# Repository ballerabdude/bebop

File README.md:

# Bebop

Bebop is a wheeled robot built on an NVIDIA Jetson AGX Thor. The current
robot (v3) is a differential-drive base: two ODrive S1 BotWheels with passive
front casters, a Robstride PowerBoard on a 13s2p Li-ion pack, two Orbbec
Gemini 335Lg depth cameras, and a Teensy 4.1 bridge for the mode button and
IMU. Everything runs on the robot, including the voice agent (TensorRT
Edge-LLM). Two Robstride arms come next; the firmware keeps its Robstride
joint path for them. The retired v2 robot was a legged humanoid; its
training and ROS 2 tooling are still in the tree.

This monorepo holds the on-robot services, the operator app and the
workstation tooling around them.

## Architecture

```
 operator app (browser: phone, tablet or desktop)
  │
  ├─ :9091 setup WS ──────────────▶ bebop-agent   Wi-Fi + Hosted Network; mode button via the Teensy
  │
  ├─ :9090 runtime WS + HTTP ─────▶ bebop-linux   100 Hz control loop, safety supervisor, system log
  │                                 ├─ SocketCAN can4 ─▶ 2× ODrive S1 (wheels)
  │                                 ├─ SocketCAN can0 ─▶ Robstride PowerBoard (battery)
  │                                 └─ systemctl ──────▶ bebop-vision, bebop-voice,
  │                                                      bebop-model-download@<id>
  ├─ :9092 video + drive notes ──┐
  ├─ :9095 places ───────────────┴▶ bebop-vision  recorder, WHEP video, place memory; owns the cameras
  ├─ :9093 voice WS ──────────────▶ bebop-voice   agent gateway: ASR → brain → TTS, or Qwen3-Omni
  └─ :9094 models HTTP ───────────▶ bebop-models  GPU budget + Edge-LLM model lifecycle
```

Every service is a systemd unit on the Thor (JetPack 7.2 / L4T R39.2.1,
CUDA 13.2, Python 3.12). The recorder and the voice agent are clients of the
runtime API too. Ports, boot order and who runs as root are in
[`docs/architecture.md`](docs/architecture.md).

## Repository layout

| Path | What it is |
|---|---|
| `firmware/bebop-linux/` | The robot runtime (Rust): SocketCAN supervisor for the ODrive wheels, the PowerBoard and the Robstride joint path; the runtime WebSocket/HTTP API on `:9090`; the always-on system log; the `sysid` single-joint actuator bench. |
| `firmware/bebop-locomotion/` | Teensy 4.1 firmware (PlatformIO). `teensy_bridge` is the production env: BNO085 IMU frames and mode-button events over USB serial. `sim` and `ros` are the legacy micro-ROS controller of an earlier wheel-legged robot (hip and knee Robstrides plus wheels); `imu_test` and `imu_spi_test` are standalone BNO085 checks (I2C, SPI). |
| `jetson-agent/` | Rust workspace: `bebop-agent` (Wi-Fi and Hosted Network provisioning, the mode button, the setup server on `:9091`), `bebop-proto` (the setup and runtime protobuf schemas), `deploy/` (agent unit and install scripts). |
| `bebop-vision/` | Python, one venv on the robot: the recorder (navd MCAP sessions), operator video (WHEP on `:9092`, `/snapshot`, drive notes), place memory (`:9095`), the voice gateway (`:9093`), the model supervisor (`:9094`) and weight downloads; plus the labeling and dataset tools (SAM 3.1 × depth labels, MCAP extraction, capture pull, session ledger). |
| `bebop-app/` | The operator app (React + TypeScript + Vite): setup wizard, driving, agent console, place memory, diagnostics, settings. `src-tauri/` is an unused Tauri 2 shell. |
| `scripts/` | `install-jetson.sh` (installs and upgrades the robot stack), `setup-rerun.sh` (on-robot MCAP → Rerun conversion), `build-gs-usb.sh`, the GPU-clocks unit, Orbbec udev rules. |
| `rerun_dashboards/` | MCAP → Rerun `.rrd` conversion and the navd and system dashboards (`open.py`). |
| `foxglove/` | Foxglove layouts: navd sessions, plus layouts for the retired v2 policy captures. |
| `sim/` | Isaac Sim / Isaac Lab training for the retired v2 humanoid (`bebop_training`), the Robstride sysid and actuator-net fitting tools, kept for the arms (`bebop_training/tools/`), and the on-device Thor training env (`setup/thor/`). |
| `ros2/` | The v2 humanoid's ROS 2 Jazzy dev workspace (URDF, `bebop_pilot`, micro-ROS agent container). Legacy. |
| `bebop-mb/` | KiCad motherboard joining the Orin Nano's 40-pin header, a Teensy 4.1, a BNO085 and a CAN transceiver. Orin Nano era. |
| `jetson-flash/` | Host-side L4T download and flash for the Orin Nano devkit. Stale for the Thor: its board config and flash commands are Orin-only. |
| `fusion-scripts/` | Fusion 360 helper scripts (hide sketches, merge bodies, rename bodies, set mass). |
| `docs/` | Cross-cutting docs; index in [`docs/README.md`](docs/README.md). |
| `docker-compose.yml` | Workstation containers `ros2_docker`, `isaac_sim`, `isaac_lab` (profiles `sim`, `lab`). |
| `Caddyfile.dev` | Dev TLS proxy for the app ([`docs/dev-https.md`](docs/dev-https.md)). |
| `justfile` | Recipes; `just` lists them. |
| `.github/workflows/ci.yml` | CI: fmt, clippy and tests for both Rust workspaces, arm64 release builds, firmware Releases on `firmware/v*` tags. |
| `AGENTS.md` | Working notes: robot access, deploy process, gotchas. |

## Getting started

[`docs/onboarding.md`](docs/onboarding.md) covers workstation setup, tests
and installing on the robot. The common recipes:

```sh
just                           # list recipes
just check                     # jetson-agent: cargo check
just test                      # jetson-agent: cargo test
just lint                      # jetson-agent: clippy, warnings are errors
just app-web                   # operator app on the Vite dev server (:1420)
just build-jetson              # bebop-agent release build (arm64 Linux only)
just deploy bebop@bebop.local  # install that bebop-agent build on the robot
just pull-data                 # mirror captures from the robot, extract, write the ledger
```

The firmware has no recipe: `cd firmware/bebop-linux && cargo test` (Linux,
`protoc` installed). On the robot, `sudo ./scripts/install-jetson.sh`
installs `bebop-agent`, `bebop-linux` and the service units.

`just fw-build` and `just fw-flash` use PlatformIO's default env (`sim`), not
the robot's `teensy_bridge`. Flash the Teensy with
`cd firmware/bebop-locomotion && pio run -e teensy_bridge --target upload`.

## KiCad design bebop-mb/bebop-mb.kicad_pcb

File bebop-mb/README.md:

# Bebop Motherboard (`bebop-mb`)

KiCad 10 project for the **Bebop Connector / motherboard** board. It is the interconnect
between an **NVIDIA Jetson Orin Nano** carrier board, a **Teensy 4.1** microcontroller, a
**Bosch BNO085 9‑DoF IMU** (Adafruit breakout), and a **CAN bus** front end. The board mostly
provides headers/breakouts and routes shared buses between these modules.

> Silkscreen title block: *"Bebop Connector"*.

## Schematic sheets

| Sheet file | Contents |
|---|---|
| `bebop-mb.kicad_sch` | Root sheet: BNO085 IMU header (`J8`) + IMU breakouts (`J11`/`J12`), CAN connectors (`J1`–`J4`), mounting holes, power |
| `teensy-mcu.kicad_sch` | Teensy 4.1 (`U1`) and its two breakout headers (`J6`/`J7`) |
| `jetson-interface.kicad_sch` | Jetson 40‑pin IDC header (`J5`) and its two breakout headers (`J9`/`J10`) |
| `can-transceiver.kicad_sch` | SN65HVD230 CAN transceiver (`U2`) + decoupling (`C14`) |

## Component / connector reference

| Ref | Part / type | Footprint | Purpose |
|---|---|---|---|
| `U1` | Teensy 4.1 (48‑pin THT, 2×24) | `bebop-mb:Teensy41_Simple` | Main MCU |
| `J6` | 1×24 socket | `PinSocket_1x24` | Teensy left row breakout (Teensy pins 1–24) |
| `J7` | 1×24 socket | `PinSocket_1x24` | Teensy right row breakout (Teensy pins 25–48) |
| `J5` | 2×20 IDC box header | `Connector_IDC:IDC-Header_2x20_P2.54mm_Vertical` | Ribbon to Jetson 40‑pin header |
| `J9` | 1×20 socket | `PinSocket_1x20` | Jetson **odd** pins (1,3,…,39) breakout |
| `J10` | 1×20 socket | `PinSocket_1x20` | Jetson **even** pins (2,4,…,40) breakout |
| `J8` | BNO085 breakout header (2×6) | `bebop-mb:BNO08x_Breakout` | Adafruit BNO085 IMU |
| `J11` | 1×6 socket | `PinSocket_1x6` | BNO085 primary‑pin breakout (VIN/3Vo/GND/SCL/SDA/INT) |
| `J12` | 1×6 socket | `PinSocket_1x6` | BNO085 secondary‑pin breakout (BT/P0/P1/RST/DI/CS) |
| `U2` | SN65HVD230 (SOIC‑8) | — | 3.3 V CAN transceiver |
| `C14` | 100 nF | `C_0603` | `U2` decoupling |
| `J1` | 3‑pin screw terminal | `TerminalBlock_Xinya XY308 3P` | CAN bus (CANH/CANL/GND) |
| `J2`,`J3`,`J4` | JST‑GH 2‑pin | `JST_GH_SM02B-GHS-TB` | CAN bus daisy‑chain (CANH/CANL) |
| `H1`–`H4` | M3 mounting holes | `MountingHole_3.2mm_M3` | Mechanical |

## Power rails

| Net | Notes |
|---|---|
| `+3.3V` | Main logic rail. Feeds BNO085 `VIN`, CAN transceiver `U2`, and the BNO `P0`/`P1` mode straps |
| `GND` | Common ground |
| `Vin` | Teensy `Vin` (broken out on `J7` pin 1) |

The Jetson 40‑pin header also exposes its own `3.3V` (pins 1, 17) and `5.0V` (pins 2, 4) on
`J9`/`J10`; these are **not** tied to the board `+3.3V` rail unless you bridge them.

---

## Teensy 4.1 (`U1`) → breakouts `J6` / `J7`

`J6`/`J7` are 1×24 socket breakouts; **`J6` pad N = Teensy pin N**, **`J7` pad N = Teensy pin N+24**.
Silkscreen on `J6`/`J7` shows the Teensy pin name.

### Active Teensy connections

| Function | Teensy pin (GPIO) | Breakout | Net |
|---|---|---|---|
| IMU SPI clock | 13 (SCK/LED) | `J7` pad 14 | `IMU_SCK` |
| IMU SPI MISO | 12 | `J6` pad 14 | `IMU_MISO` |
| IMU SPI MOSI | 11 | `J6` pad 13 | `IMU_MOSI` |
| IMU SPI CS | 10 | `J6` pad 12 | `IMU_CS` |
| IMU interrupt | 37 | `J7` pad 20 | `IMU_INT` |
| IMU reset | 36 | `J7` pad 21 | `IMU_RST` |
| CAN1 TX (CTX1) | 22 | `J7` pad 5 | `CAN1_TX` |
| CAN1 RX (CRX1) | 23 | `J7` pad 4 | `CAN1_RX` |
| I²C SCL (spare) | 19 (A5/SCL) | `J7` pad 8 | `IMU_SCL` |
| I²C SDA (spare) | 18 (A4/SDA) | `J7` pad 9 | `IMU_SDA` |

> `IMU_SCL`/`IMU_SDA` are the legacy I²C pins. The IMU was migrated to **SPI**, so these are
> now just an unused I²C bus broken out on `J7`.

---

## BNO085 IMU (`J8`) — wired for SPI

The BNO085 is configured for **SPI** (not I²C). Protocol is selected by tying `P0`/`P1` high.

| `J8` pin | BNO pad | SPI role | Net |
|---|---|---|---|
| 1 | VIN | power | `+3.3V` |
| 3 | GND | ground | `GND` |
| 4 | SCL | SCK (clock) | `IMU_SCK` |
| 5 | SDA | MISO (sensor → host) | `IMU_MISO` |
| 11 | DI | MOSI (host → sensor) | `IMU_MOSI` |
| 12 | CS | chip select | `IMU_CS` |
| 6 | INT | data‑ready | `IMU_INT` |
| 10 | RST | reset | `IMU_RST` |
| 8 | P0 (PS0) | mode select → **high** | `+3.3V` |
| 9 | P1 (PS1) | mode select → **high** | `+3.3V` |
| 2 | 3Vo | BNO 3.3 V out (breakout only) | — |
| 7 | BT | boot (breakout only) | `J12` pin 1 |

`J11` breaks out the primary row (VIN/3Vo/GND/SCL/SDA/INT) and `J12` the secondary row
(BT/P0/P1/RST/DI/CS); both simply follow whatever `J8` carries.

---

## Shared IMU SPI bus (Teensy **and** Jetson)

The BNO085 SPI bus is wired **in parallel** to both the Teensy and the Jetson so either can act
as master. They must **not** be active at the same time.

```
            IMU_SCK / IMU_MISO / IMU_MOSI / IMU_CS / IMU_INT / IMU_RST
                                  |
        +---------------+---------+---------+----------------+
        |               |                   |                |
   BNO085 (J8)     Teensy U1           Jetson J5         Breakouts
                (13/12/11/10,        (SPI0 + GPIO,      (J6/J7, J9/J10,
                 37/36)               see below)         J11/J12)
```

| Signal | BNO085 | Teensy 4.1 | Jetson 40‑pin |
|---|---|---|---|
| SCK | SCL | GPIO13 | pin 23 (SPI0_SCK) |
| MISO | SDA | GPIO12 | pin 21 (SPI0_MISO) |
| MOSI | DI | GPIO11 | pin 19 (SPI0_MOSI) |
| CS | CS | GPIO10 | pin 24 (SPI0_CS0\*) |
| INT | INT | GPIO37 | pin 7 (GPIO09) |
| RST | RST | GPIO36 | pin 15 (GPIO12) |

> ⚠️ **Bus contention:** there is no hardware isolation (no mux/buffer) between the two masters.
> Firmware must keep the **inactive** master's SCK/MOSI/CS (and INT/RST) pins as **high‑impedance
> inputs** so the two masters never drive the bus simultaneously.

---

## Jetson 40‑pin header (`J5`) → breakouts `J9` / `J10`

`J5` is a 2×20 IDC box header (ribbon to the Jetson carrier 40‑pin expansion header).
`J9` breaks out the **odd** column, `J10` the **even** column. Silkscreen on `J9`/`J10` is
`<Jetson pin #> <signal>`.

| Pin | Signal | | Pin | Signal |
|---:|---|---|---:|---|
| 1 | 3.3V | | 2 | 5.0V |
| 3 | I2C1_SDA | | 4 | 5.0V |
| 5 | I2C1_SCL | | 6 | GND |
| 7 | GPIO09 → **IMU_INT** | | 8 | UART1_TXD |
| 9 | GND | | 10 | UART1_RXD |
| 11 | UART1_RTS\* | | 12 | I2S0_SCLK |
| 13 | SPI1_SCK | | 14 | GND |
| 15 | GPIO12 → **IMU_RST** | | 16 | SPI1_CS1\* |
| 17 | 3.3V | | 18 | SPI1_CS0\* |
| 19 | SPI0_MOSI → **IMU_MOSI** | | 20 | GND |
| 21 | SPI0_MISO → **IMU_MISO** | | 22 | SPI1_MISO |
| 23 | SPI0_SCK → **IMU_SCK** | | 24 | SPI0_CS0\* → **IMU_CS** |
| 25 | GND | | 26 | SPI0_CS1\* |
| 27 | I2C0_SDA | | 28 | I2C0_SCL |
| 29 | GPIO01 | | 30 | GND |
| 31 | GPIO11 | | 32 | GPIO07 |
| 33 | GPIO13 | | 34 | GND |
| 35 | I2S0_FS | | 36 | UART1_CTS\* |
| 37 | SPI1_MOSI | | 38 | I2S0_DIN |
| 39 | GND | | 40 | I2S0_DOUT |

Pins in **bold** are routed to the shared IMU bus; all other pins are simply broken out on
`J9`/`J10` for access.

---

## CAN bus (`U2` + `J1`–`J4`)

`U2` (SN65HVD230, 3.3 V) bridges the Teensy CAN1 controller to the physical bus.

| `U2` side | Connects to |
|---|---|
| `D` (driver in) | `CAN1_TX` ← Teensy GPIO22 (CTX1) |
| `R` (receiver out) | `CAN1_RX` → Teensy GPIO23 (CRX1) |
| `CANH` / `CANL` | CAN connectors `J1`–`J4` |
| `VCC` / `GND` | `+3.3V` / `GND` |

- `J1` — 3‑pin screw terminal: **CANH / CANL / GND**.
- `J2`, `J3`, `J4` — JST‑GH 2‑pin: **CANH / CANL** (for daisy‑chaining nodes).

Add a 120 Ω termination resistor at the bus ends as needed (not currently populated on‑board).

---

## Notes

- This board is KiCad 10 (name‑based nets; no numbered net table).
- After editing any schematic sheet, run **Tools → Update PCB from Schematic** and re‑run **DRC**.
- The IMU SPI bus sharing relies on firmware discipline (see the contention warning above); if you
  want hardware‑guaranteed isolation, add series resistors or a GPIO/jumper‑selected SPI bus switch.

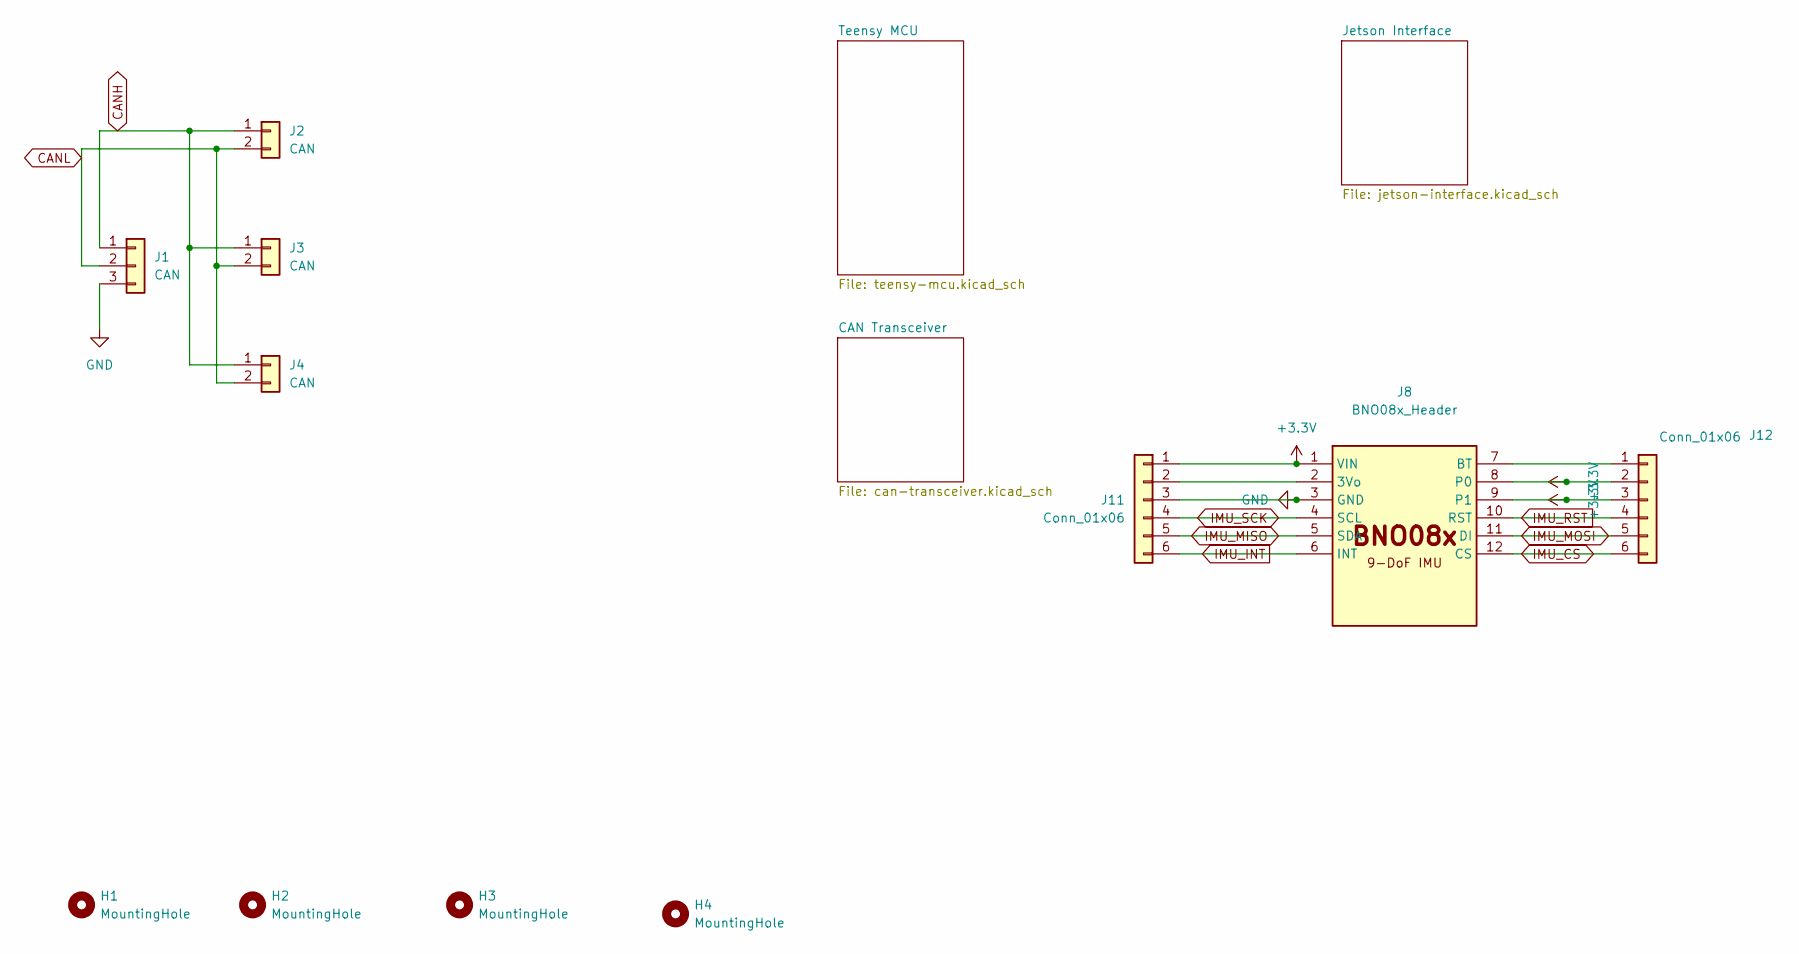
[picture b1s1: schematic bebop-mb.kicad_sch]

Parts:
H1, H2, H3, H4: MountingHole; MountingHole_3.2mm_M3_ISO14580
J1: CAN; TerminalBlock_Xinya_XY308-2.54-3P_1x03_P2.54mm_Horizontal; Manufacturer Part Number XY308-3P
J2, J3, J4: CAN; JST_GH_SM02B-GHS-TB_1x02-1MP_P1.25mm_Horizontal; Manufacturer Part Number SM02B-GHS-TB(LF)(SN)
J8: BNO08x_Header; BNO08x_Breakout; Manufacturer Part Number PPTC061LFBN-RC
J11, J12: Conn_01x06; PinSocket_1x06_P2.54mm_Vertical; Manufacturer Part Number PPTC061LFBN-RC

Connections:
+3.3V: J8.1 (VIN), J8.8 (P0), J8.9 (P1), J11.1, J12.2, J12.3; also elsewhere on the board
CANH: J1.1, J2.1, J3.1, J4.1; also elsewhere on the board
CANL: J1.2, J2.2, J3.2, J4.2; also elsewhere on the board
GND: J1.3, J8.3 (GND), J11.3; also elsewhere on the board
IMU_CS: J8.12 (CS), J12.6; also elsewhere on the board
IMU_INT: J8.6 (INT), J11.6; also elsewhere on the board
IMU_MISO: J8.5 (SDA), J11.5; also elsewhere on the board
IMU_MOSI: J8.11 (DI), J12.5; also elsewhere on the board
IMU_RST: J8.10 (RST), J12.4; also elsewhere on the board
IMU_SCK: J8.4 (SCL), J11.4; also elsewhere on the board
unnamed: J8.2 (3Vo), J11.2
unnamed: J8.7 (BT), J12.1

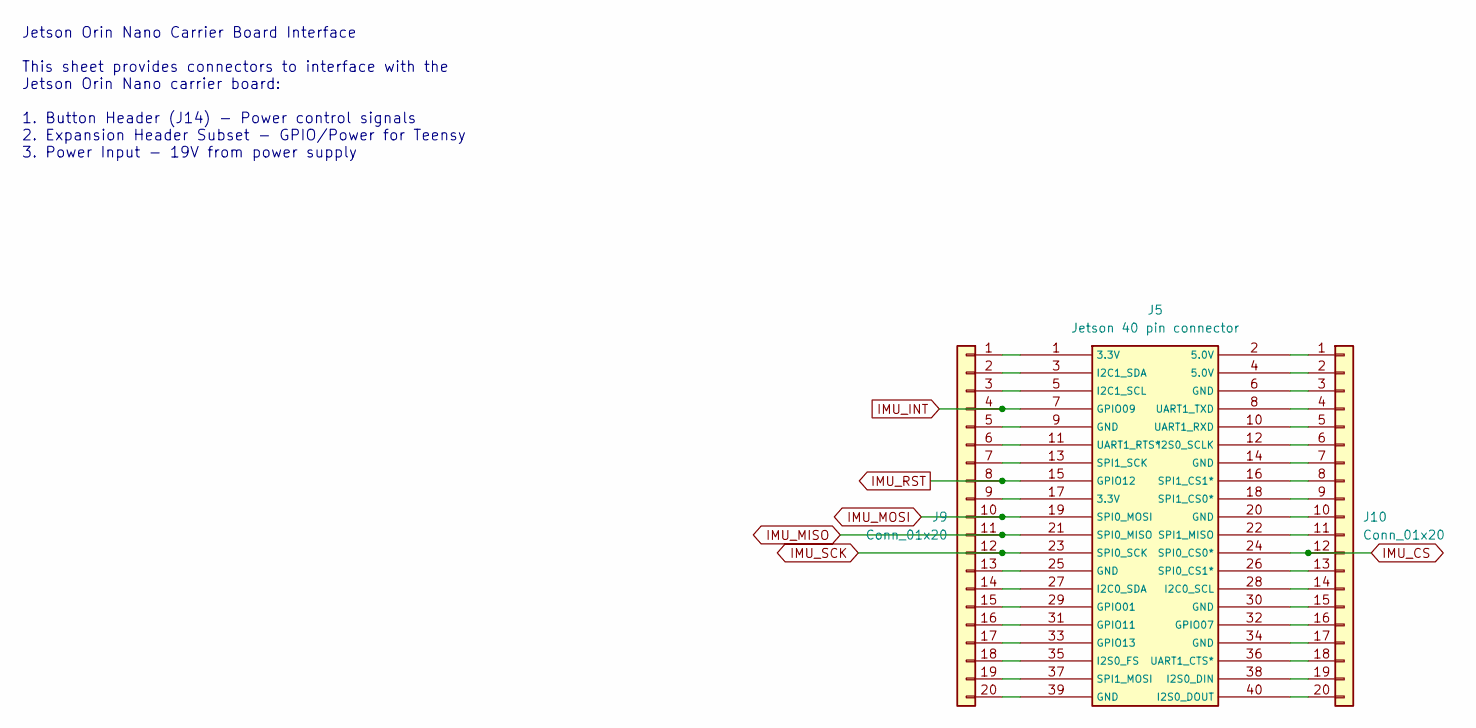
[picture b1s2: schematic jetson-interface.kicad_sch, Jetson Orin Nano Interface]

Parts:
J5: Jetson 40 pin connector; IDC-Header_2x20_P2.54mm_Vertical; Manufacturer Part Number PPTC202LFBN-RC
J9, J10: Conn_01x20; PinSocket_1x20_P2.54mm_Vertical; Manufacturer Part Number PPTC201LFBN-RC

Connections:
IMU_CS: J5.24 (SPI0_CS0*), J10.12; also elsewhere on the board
IMU_INT: J5.7 (GPIO09), J9.4; also elsewhere on the board
IMU_MISO: J5.21 (SPI0_MISO), J9.11; also elsewhere on the board
IMU_MOSI: J5.19 (SPI0_MOSI), J9.10; also elsewhere on the board
IMU_RST: J5.15 (GPIO12), J9.8; also elsewhere on the board
IMU_SCK: J5.23 (SPI0_SCK), J9.12; also elsewhere on the board
unnamed: J5.29 (GPIO01), J9.15
unnamed: J5.31 (GPIO11), J9.16
unnamed: J5.33 (GPIO13), J9.17
unnamed: J5.27 (I2C0_SDA), J9.14
unnamed: J5.5 (I2C1_SCL), J9.3
unnamed: J5.3 (I2C1_SDA), J9.2
unnamed: J5.35 (I2S0_FS), J9.18
unnamed: J5.37 (SPI1_MOSI), J9.19
unnamed: J5.13 (SPI1_SCK), J9.7
unnamed: J5.11 (UART1_RTS*), J9.6
unnamed: J5.1 (3.3V), J9.1
unnamed: J5.9 (GND), J9.5
unnamed: J5.17 (3.3V), J9.9
unnamed: J5.25 (GND), J9.13
unnamed: J5.39 (GND), J9.20
unnamed: J5.2 (5.0V), J10.1
unnamed: J5.4 (5.0V), J10.2
unnamed: J5.6 (GND), J10.3
unnamed: J5.8 (UART1_TXD), J10.4
unnamed: J5.10 (UART1_RXD), J10.5
unnamed: J5.12 (I2S0_SCLK), J10.6
unnamed: J5.14 (GND), J10.7
unnamed: J5.16 (SPI1_CS1*), J10.8
unnamed: J5.18 (SPI1_CS0*), J10.9
unnamed: J5.20 (GND), J10.10
unnamed: J5.22 (SPI1_MISO), J10.11
unnamed: J5.26 (SPI0_CS1*), J10.13
unnamed: J5.28 (I2C0_SCL), J10.14
unnamed: J5.30 (GND), J10.15
unnamed: J5.32 (GPIO07), J10.16
unnamed: J5.34 (GND), J10.17
unnamed: J5.36 (UART1_CTS*), J10.18
unnamed: J5.38 (I2S0_DIN), J10.19
unnamed: J5.40 (I2S0_DOUT), J10.20

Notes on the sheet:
Jetson Orin Nano Carrier Board Interface This sheet provides connectors to interface with the Jetson Orin Nano carrier board: 1. Button Header (J14) - Power control signals 2. Expansion Header Subset - GPIO/Power for Teensy 3. Power Input - 19V from power supply

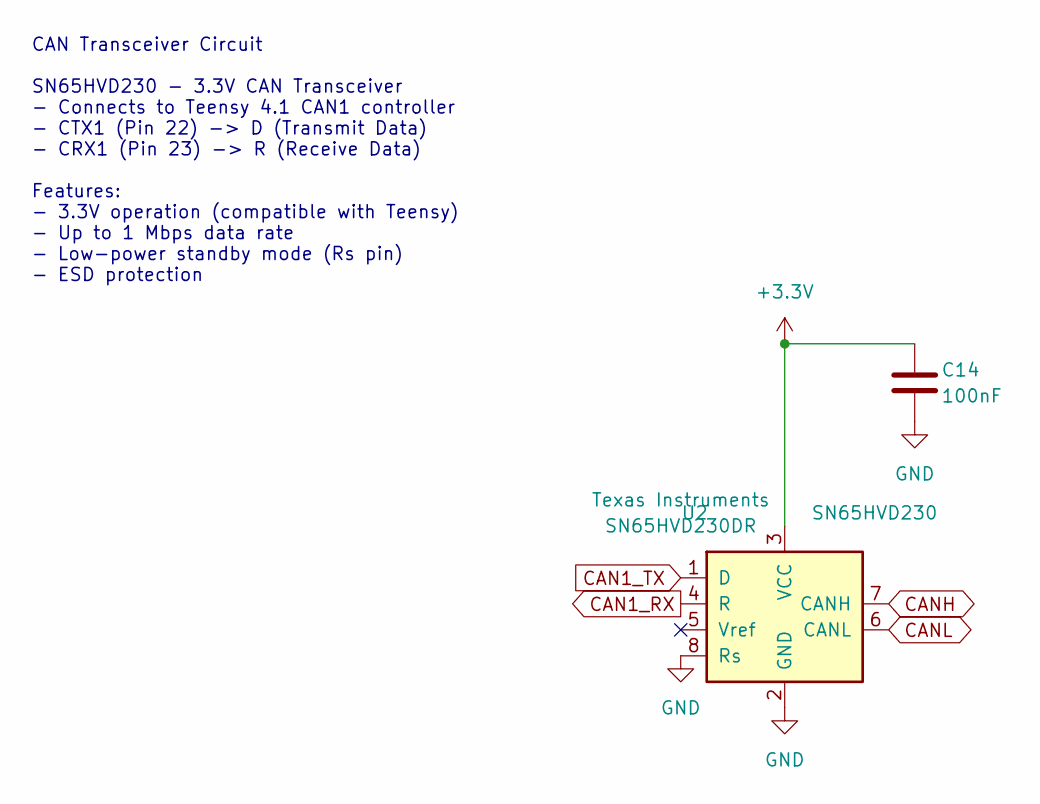
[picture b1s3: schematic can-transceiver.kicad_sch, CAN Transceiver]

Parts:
C14: 100nF; C_0603_1608Metric; Manufacturer Part Number GRM188R71H104KA93D
U2: SN65HVD230; SOIC-8_3.9x4.9mm_P1.27mm; Manufacturer Part Number SN65HVD230DR

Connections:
+3.3V: C14.1, U2.3 (VCC); also elsewhere on the board
CAN1_RX: U2.4 (R); also elsewhere on the board
CAN1_TX: U2.1 (D); also elsewhere on the board
CANH: U2.7 (CANH); also elsewhere on the board
CANL: U2.6 (CANL); also elsewhere on the board
GND: C14.2, U2.2 (GND), U2.8 (Rs); also elsewhere on the board

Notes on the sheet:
CAN Transceiver Circuit SN65HVD230 - 3.3V CAN Transceiver - Connects to Teensy 4.1 CAN1 controller - CTX1 (Pin 22) -> D (Transmit Data) - CRX1 (Pin 23) -> R (Receive Data) Features: - 3.3V operation (compatible with Teensy) - Up to 1 Mbps data rate - Low-power standby mode (Rs pin) - ESD protection

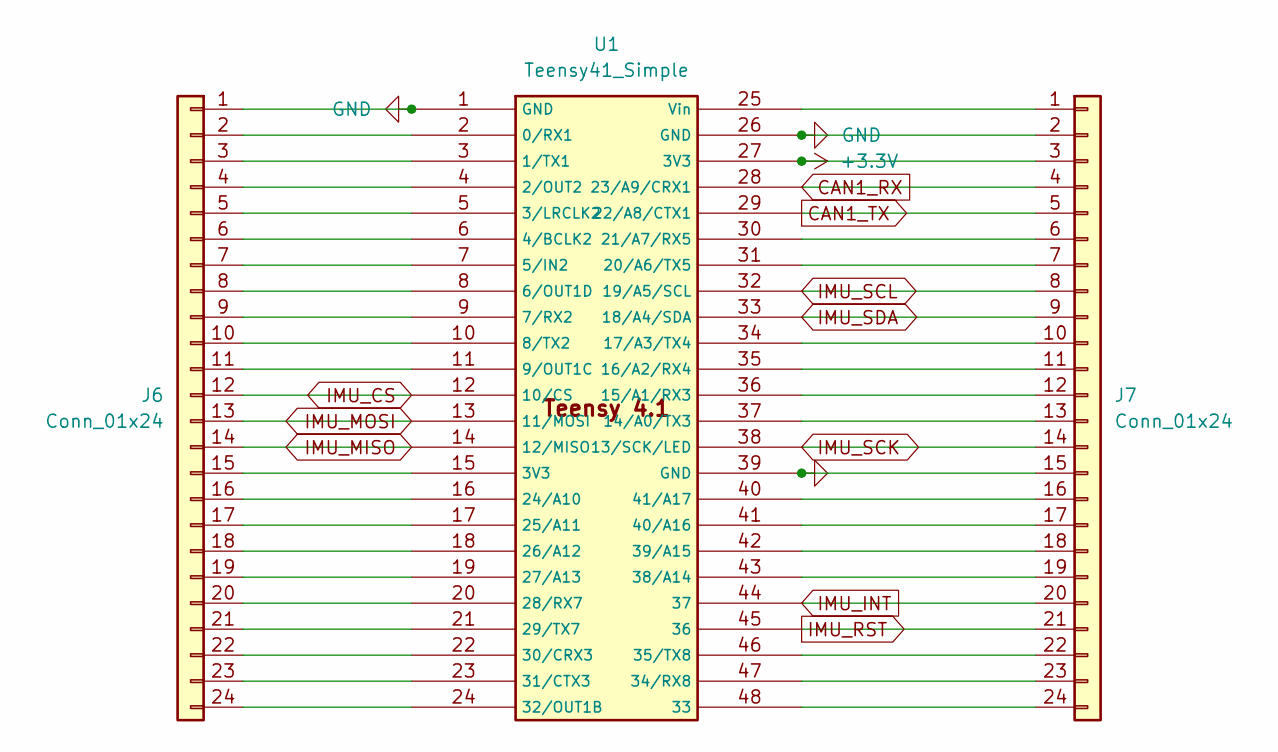
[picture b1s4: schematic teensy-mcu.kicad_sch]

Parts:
J6, J7: Conn_01x24; PinSocket_1x24_P2.54mm_Vertical; Manufacturer Part Number PPTC241LFBN-RC
U1: Teensy41_Simple; Manufacturer Part Number PPTC241LFBN-RC

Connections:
+3.3V: J7.3, U1.27 (3V3); also elsewhere on the board
CAN1_RX: J7.4, U1.28 (23/A9/CRX1); also elsewhere on the board
CAN1_TX: J7.5, U1.29 (22/A8/CTX1); also elsewhere on the board
GND: J6.1, J7.2, J7.15, U1.1 (GND), U1.26 (GND), U1.39 (GND); also elsewhere on the board
IMU_CS: J6.12, U1.12 (10/CS); also elsewhere on the board
IMU_INT: J7.20, U1.44 (37); also elsewhere on the board
IMU_MISO: J6.14, U1.14 (12/MISO); also elsewhere on the board
IMU_MOSI: J6.13, U1.13 (11/MOSI); also elsewhere on the board
IMU_RST: J7.21, U1.45 (36); also elsewhere on the board
IMU_SCK: J7.14, U1.38 (13/SCK/LED); also elsewhere on the board
IMU_SCL: J7.8, U1.32 (19/A5/SCL)
IMU_SDA: J7.9, U1.33 (18/A4/SDA)
unnamed: J6.2, U1.2 (0/RX1)
unnamed: J6.3, U1.3 (1/TX1)
unnamed: J6.4, U1.4 (2/OUT2)
unnamed: J6.5, U1.5 (3/LRCLK2)
unnamed: J6.6, U1.6 (4/BCLK2)
unnamed: J6.7, U1.7 (5/IN2)
unnamed: J6.8, U1.8 (6/OUT1D)
unnamed: J6.9, U1.9 (7/RX2)
unnamed: J6.10, U1.10 (8/TX2)
unnamed: J6.11, U1.11 (9/OUT1C)
unnamed: J6.15, U1.15 (3V3)
unnamed: J6.16, U1.16 (24/A10)
unnamed: J6.17, U1.17 (25/A11)
unnamed: J6.18, U1.18 (26/A12)
unnamed: J6.19, U1.19 (27/A13)
unnamed: J6.20, U1.20 (28/RX7)
unnamed: J6.21, U1.21 (29/TX7)
unnamed: J6.22, U1.22 (30/CRX3)
unnamed: J6.23, U1.23 (31/CTX3)
unnamed: J6.24, U1.24 (32/OUT1B)
unnamed: J7.1, U1.25 (Vin)
unnamed: J7.6, U1.30 (21/A7/RX5)
unnamed: J7.7, U1.31 (20/A6/TX5)
unnamed: J7.10, U1.34 (17/A3/TX4)
unnamed: J7.11, U1.35 (16/A2/RX4)
unnamed: J7.12, U1.36 (15/A1/RX3)
unnamed: J7.13, U1.37 (14/A0/TX3)
unnamed: J7.16, U1.40 (41/A17)
unnamed: J7.17, U1.41 (40/A16)
unnamed: J7.18, U1.42 (39/A15)
unnamed: J7.19, U1.43 (38/A14)
unnamed: J7.22, U1.46 (35/TX8)
unnamed: J7.23, U1.47 (34/RX8)
unnamed: J7.24, U1.48 (33)

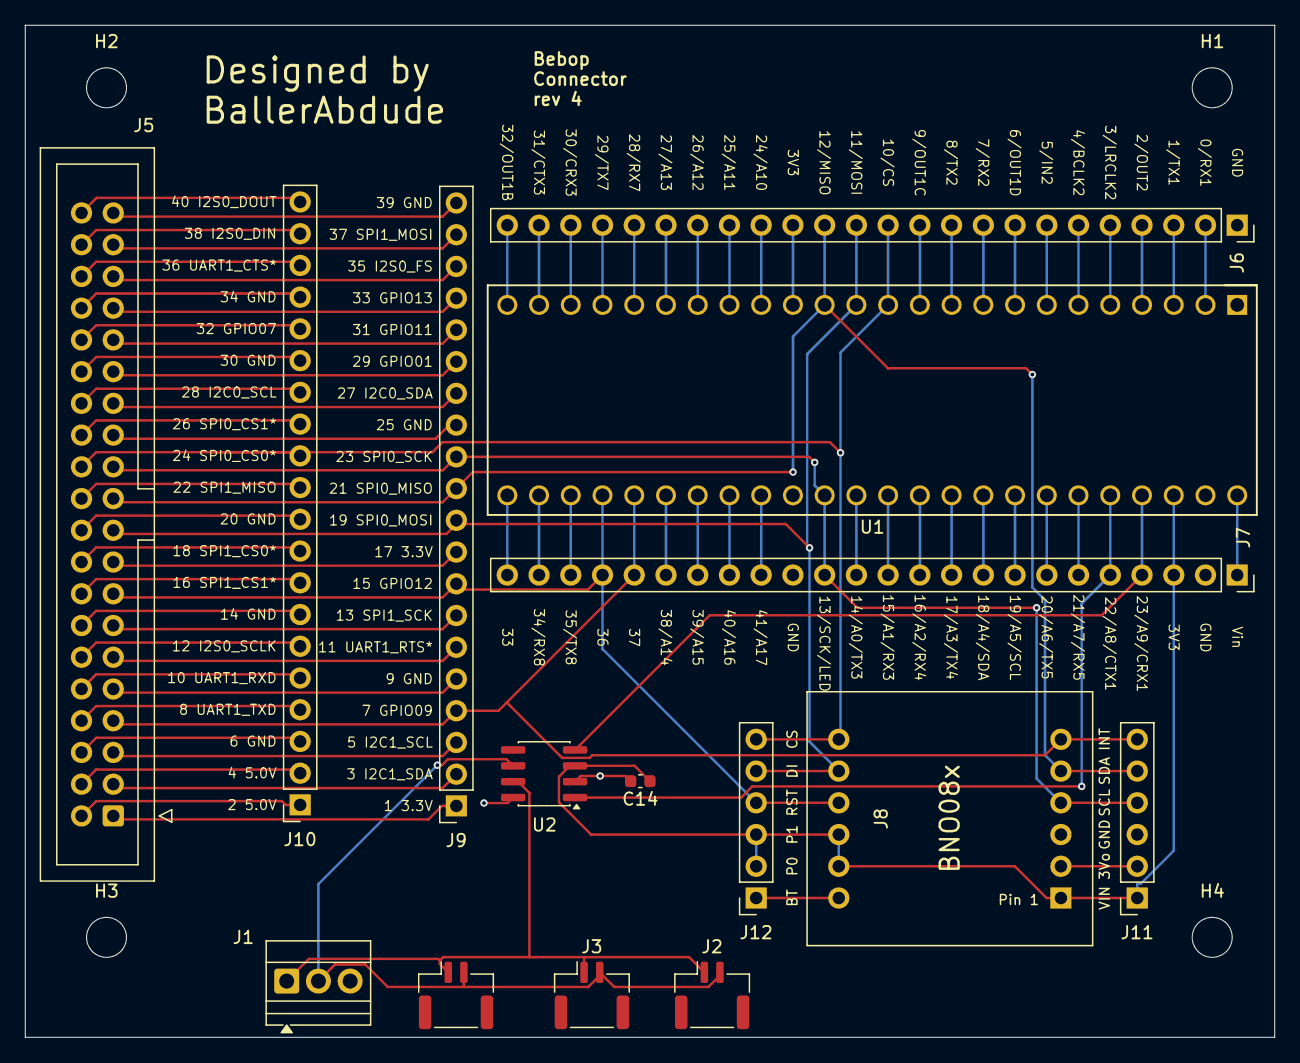
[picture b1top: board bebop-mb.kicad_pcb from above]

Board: 2 copper layers, 100.0 x 81.0 mm, 19 parts (0 on the bottom side), 84 nets.

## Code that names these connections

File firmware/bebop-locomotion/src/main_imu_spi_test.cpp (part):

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// CONFIGURATION
// ============================================================================

#define IMU_CS_PIN    10       // SPI chip select
#define IMU_INT_PIN   37       // REQUIRED for SPI
#define IMU_RST_PIN   36       // reset (constructor)
#define REPORT_INTERVAL_US 5000   // 5ms -> 200Hz requested report rate

// Use the primary USB serial for all output.
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// ============================================================================

// Reset pin is supplied to the constructor; CS/INT go to begin_SPI().
Adafruit_BNO08x bno(IMU_RST_PIN);
sh2_SensorValue_t sensorValue;

float quat_w = 1, quat_x = 0, quat_y = 0, quat_z = 0;
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// low when it has data to send / is ready. If INT never moves, the sensor is
// likely unpowered, not in SPI mode (PS1/PS0), or INT is miswired.
void probeIntPin() {
    pinMode(IMU_INT_PIN, INPUT_PULLUP);
    OUT.printf("[SPI] Sampling INT pin (%d) for 500ms...\n", IMU_INT_PIN);
    int lows = 0, highs = 0;
    uint32_t t0 = millis();
    while (millis() - t0 < 500) {
        if (digitalRead(IMU_INT_PIN) == LOW) lows++; else highs++;
        delayMicroseconds(200);
    }
    OUT.printf("[SPI]   INT samples: LOW=%d HIGH=%d %s\n", lows, highs,
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    probeIntPin();

    OUT.printf("[IMU] Initializing BNO085 over SPI (CS=%d, INT=%d, RST=%d)...\n",
               IMU_CS_PIN, IMU_INT_PIN, IMU_RST_PIN);

    if (!bno.begin_SPI(IMU_CS_PIN, IMU_INT_PIN, &SPI)) {
        OUT.println(F("[IMU] begin_SPI() FAILED."));
        OUT.println(F("[IMU]   -> Confirm PS1=1, PS0=1 (SPI mode)."));
        OUT.println(F("[IMU]   -> Confirm SCK=13, MOSI=11, MISO=12, CS, INT, RST."));
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    // read entirely when INT is high.
    int drained = 0;
    while (drained < MAX_EVENTS_PER_LOOP &&
           digitalRead(IMU_INT_PIN) == LOW &&
           bno.getSensorEvent(&sensorValue)) {
        drained++;
        event_count++;
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
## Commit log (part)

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2026-04-30 style(jetson-agent): apply rustfmt to ble::server
    Reflows three method chains in `bebop-agent/src/ble/server.rs` that the
    current pinned rustfmt (1.90.0) collapses onto a single line. No
    semantic changes; `cargo fmt --all -- --check` is now clean across the
    workspace.
2026-05-01 ci(jetson-agent): install modern protoc in cross image
    The default `cross` aarch64-unknown-linux-gnu image is based on Ubuntu
    16.04, whose `protobuf-compiler` package is protoc 2.6.1 and rejects
    `syntax = "proto3"`. Drop the apt package and fetch a current protoc
    release binary into /usr/local during pre-build so bebop-proto's
    build.rs can compile bebop.proto under cross.
    Made-with: Cursor
2026-05-01 chore(jetson-agent): mark deploy scripts executable
    So `sudo ./jetson-agent/deploy/scripts/install.sh ...` works directly
    on a fresh clone without needing `chmod +x` first (or invoking via
    `bash`). Matches how every other shell entrypoint in the repo is
    expected to be run.
    Made-with: Cursor
2026-05-01 fix(bebop-app): improve Wi-Fi network selection UX
    The picker was confusing in real environments:
    - Multi-AP and dual-band networks showed up multiple times because nmcli
    returns one row per BSSID. Dedupe by (ssid, security), keeping the
    strongest signal, so each SSID renders once.
    - Tapping the already-connected network walked the user through the
    password prompt again, even though the agent already has working
2026-05-01 fix(bebop-app): make BLE transport reliable and friendly
    A handful of bugs surfaced while exercising the setup flow on real
    hardware. They all sit in the BLE transport layer and the screens that
    drive it; bundling here so each individual fix has the others as
    context.
    Tauri / btleplug central (src-tauri/src/ble/central.rs):
    - Open the notification stream synchronously inside connect() before
2026-05-05 ci: build bebop-linux alongside bebop-agent
    Mirrors the agent's two-job pattern (host checks + native arm64
    build) for firmware/bebop-linux so every push produces both a
    bebop-agent-aarch64 and bebop-linux-aarch64 artifact ready to
    deploy to a Jetson.
2026-05-06 fix(ci): satisfy cargo fmt and clippy --workspace -- -D warnings
    - firmware: apply rustfmt across recent changes
    - firmware: fix clippy lints (iter_cloned_collect, let_and_return,
    useless_vec, needless_range_loop)
    - jetson-agent: replace evdev::KeyCode::BTN_GAMEPAD/BTN_JOYSTICK (not
    exported in evdev 0.13) with their canonical aliases BTN_SOUTH/
    BTN_TRIGGER
2026-05-06 feat(deploy): one-shot Jetson installer + bebop-linux systemd unit
    scripts/install-jetson.sh pulls the latest green-on-main bebop-agent
    and bebop-linux artifacts from CI (via gh) and lays them down with
    their systemd units and config templates. Idempotent; existing
    /etc/bebop/agent.toml and /etc/bebop/bebop_v2.yaml are preserved.
    --setup-can / --setup-can-only handles the candleLight USB-CAN hub
    on the Orin Nano: blacklists mttcan to free can0, persists gs_usb,
2026-05-06 feat(bebop-app): expose Bluetooth controller setup from the motor bench
    Previously the controller pairing screen was reachable only from the
    Dashboard (BLE flow). Add a "Bluetooth controller" link to the Motor
    Bench too, and make the controllers screen's back button return to
    wherever the user came from (dashboard or motor bench).
2026-05-06 fix(agent): keep running when docker is unavailable
2026-05-06 fixed fmt error
2026-05-08 feat(bebop-app): Bluetooth gamepad dial-in + mobile motor bench
    Adds a Web Gamepad API driver that lets a phone- or laptop-paired
    controller drive the active joint's target on the motor bench, with
    auto-detection between standard and dinput HID layouts. Reworks the
    motor bench and IP-connect screens for phone-sized viewports
    (stacked motor cards, full-width segmented mode switcher, prominent
    E-STOP, hostname-friendly IP input). Firmware gets per-joint
2026-05-10 Updated URDF
2026-05-10 feat(sim): add train_bebop.py entry point + document training curriculum - sim/train_bebop.py: rsl_rl PPO training entry point. Avoids the AppLauncher double-init crash by reading task spec via gym.s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
2026-05-10 fix(bebop-linux): switch ort to load-dynamic so CI links on glibc 2.35
    CI is pinned to ubuntu-22.04-arm (glibc 2.35) for JetPack 6 compatibility,
    but the default `download-binaries` feature pulls a prebuilt onnxruntime
    blob compiled against newer glibc / libstdc++ — the link step fails with
    undefined references to `__isoc23_strtol*` (glibc 2.38) and
    `__cxa_call_terminate` (newer libstdc++).
    `load-dynamic` builds against ort headers only and `dlopen`s
2026-05-11 added missing model file
2026-05-12 Configure IMU mount orientation
    Apply the BNO08x sensor-to-body mount rotation in firmware, normalize published IMU quaternions, and update the orientation widget to render body-frame attitude correctly.
2026-05-12 vendor(bno08x-rs): fork 2.0.1 with patches for SH-2 0x28 + Send
    The production bebop-linux IMU path needs SH-2 sensor report 0x28
    (AR/VR-Stabilized Rotation Vector) -- the magnetometer-fused but EMI-
    hardened replacement for 0x05 that the old Teensy firmware in
    firmware/bebop-locomotion/include/BNO085_IMU.h has been using all
    along. The crates.io copy of bno08x-rs (v2.0.1) physically cannot
    deliver it:
2026-05-12 Updated install scripts
2026-05-13 resolved some build errors
2026-05-14 firmware(bebop-linux): retrain policy + supporting runtime/safety changes
2026-05-15 vendor(bno08x-rs): bounds-check SHTP advertisement TLV parser
    handle_advertise_response's `while cursor < payload_len` was
    off-by-one for the 2-byte (tag,len) header and panicked with
    `index out of bounds` on the final TLV of a full ~1.2 KB advert.
    Tighten the bound to `cursor + 1 < payload_len` and bail on a
    length field that would walk past the slice end. Add as
    BEBOP-PATCH [5/5] in PATCHES.md and renumber existing markers.
2026-05-15 firmware(safety): latch E-STOP on Robstride fault frames, accept active-reports
    Add a MotorFaultReport BreachReason carrying the raw 8-byte payload
    plus best-effort decode of the status bits visible in the CAN ID.
    Wire the RX thread to dispatch on cmd_type: 0x02 / 0x18 go through
    on_feedback (active-report shares the feedback wire format), 0x15
    triggers on_fault_report and latches E-STOP, anything else from a
    known motor is debug-logged. Previously 0x15 was dropped on the
2026-05-15 config(bebop_v2): pin firmware tau_max to sim FW_*_TAU_MAX (trained envelope)
    Update the rationale comments on both sides to make explicit that
    the supervisor's hard_limits.tau_max MUST equal the matching
    FW_*_TAU_MAX in bebop_v2_base_cfg.py — the policy was trained
    against exactly that envelope (effort_limit_sim), so any drift
    means deploy-time torques the policy didn't see or supervisor
    trips on torques it was trained to use. Document the per-group
2026-05-16 updated confirm code
2026-05-17 updated model
2026-05-19 sim+firmware(bebop-v2): merge push-recovery into balance task and overhaul reward shaping
    Collapse the staged Flat -> FlatRobust curriculum into a single
    balance task that handles both standing in place and recovering from
    lateral pushes.
    - VariableImpedanceJointAction.reset: seed slew tracker and delay
    ring buffer from the current joint pose (not the default pose).
    Without this, the high-stiffness actuator snapped every randomized
2026-05-21 sim(bebop-v2): minimal standing experiment + 7kg torso mass correction Bench measurement showed the real torso is 7.0 kg, not the 10.5 kg the CAD-derived USD claimed. Combined with the kitchen-sink c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
2026-05-21 Harden BNO08x SPI bring-up with extended reset and INT pull-up.
    Add BEBOP-PATCH [6/6]: 10 ms RST settle/hold, 3 s HINTN wake timeout,
    and explicit Bias::PullUp on the INT line to reduce spurious bring-up
    failures on cold boot and EMI-heavy wiring.
2026-05-21 sim+firmware(bebop-v2): v0.7/v0.8 standing — recovery + knee symmetry
    The v0.6 deployed policy stood "calm" in a slight forward lean but
    fell to the slightest backward tilt — the foot center is forward of
    the torso CoM (v0.1 note), so backward is the unstable direction,
    and the policy had only seen ±2° pitch at init with no mid-episode
    pushes. Then the v0.7 fix surfaced a second failure mode the rewards
    were blind to: an asymmetric crouch where one knee did all the work
2026-05-23 Updated Robot design
2026-05-23 sim(bebop-v2): v0.9 — rename joints to match anatomical URDF
    Renames the leg chain across the training package in lockstep with the
    new URDF / USD: hip_abduction_*_joint -> hip_flexion_*_joint,
    femur_*_joint -> hip_abduction_*_joint, shin_*_joint ->
    knee_flexion_*_joint. JOINT_NAMES_ALL index order is unchanged, so the
    24-dim MIT action / 52-dim observation contract and the trained v0.8
    ONNX architecture stay binary-compatible — only the joint name strings
2026-05-23 Exported Isaac-BebopV2-Standing-v0/2026-05-23_06-08-33/model_8000.pt
2026-06-02 firmware(bebop-linux): add serial IMU backend reading the Teensy bridge
    Add `imu.source: serial` as an alternative to the direct-SPI BNO085
    reader. imu_serial.rs opens the Teensy USB-serial port, CRC-checks the
    binary frames, and fills the same ImuShared snapshot, reusing imu.rs's
    mount/normalize math so the two sources are interchangeable for the
    policy runner and telemetry. Adds the serialport dep and config plumbing.
2026-06-02 firmware(bebop-locomotion): BNO085 SPI driver, 200Hz reports, USB IMU bridge
    Migrate the BNO085 driver from I2C to SPI (dedicated INT line, AR/VR
    stabilized RV 0x28) and bump the requested report rate from 100Hz to
    200Hz. Add an `imu_bridge` build that streams fused orientation + gyro +
    accel to the Jetson over USB serial as fixed 52-byte binary frames
    (see ImuSerialProtocol.h), plus the standalone SPI/I2C IMU test programs
    and their PlatformIO envs.
2026-06-02 updated imu bridge
2026-06-03 Apply sysid-measured actuator params + harden sysid tool
    Plug sysid-measured Coulomb friction and reflected rotor inertia (armature)
    into the four DCMotorCfg groups in exp_standing.py (right-side bench runs),
    keeping stall torque / no-load speed at datasheet values (encoder-saturated /
    unblocked on the bench). Add a randomize_joint_parameters reset event that
    scales friction x[0.7,1.4] and armature x[0.9,1.1] about the measured nominal.
    Harden the sysid binary: split immediate (fault/comms) vs debounced kinematic
2026-06-10 added documentation for the motherboard
2026-06-12 feat(bebop-linux): MCAP policy capture + dry-run, drop gyro_live signal
    Operator-toggled observation/action capture for noise review and sim
    playback, plus a "dry run" flag that lets the policy infer + record
    without driving the actuators.
    bebop-linux
    - New `policy_capture` writer thread: bounded mpsc + dedicated
    `mcap::Writer<BufWriter<File>>` with Zstd chunks, off the 100 Hz
2026-06-13 feat(bebop-linux): always-on MCAP capture with size-based rotation, HTTP downloads, and WS auto-reconnect
    Capture now runs automatically whenever the runtime is in DIAL_IN or
    RUN_POLICY and is not E-STOPped; the operator no longer toggles it.
    The writer auto-rotates the active file at 256 MiB and prunes oldest
    segments to keep the capture dir under a 4 GiB total budget, so a
    robot left on for hours never fills the eMMC. The runner throttles
    its open requests to once every 5 s and the writer dedupes identical
2026-06-14 Updated foxglove layouts
